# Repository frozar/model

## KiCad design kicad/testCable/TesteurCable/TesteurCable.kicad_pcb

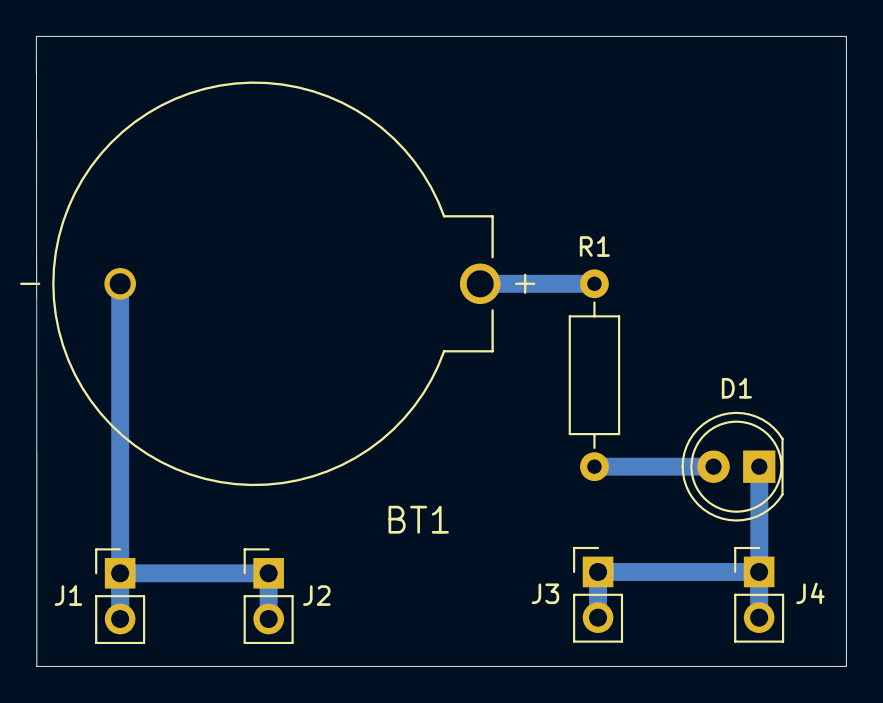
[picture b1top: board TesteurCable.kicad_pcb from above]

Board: 2 copper layers, 45.0 x 35.0 mm, 7 parts (0 on the bottom side), 4 nets.

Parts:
BT1: BS-7; BAT_BS-7
D1: LED_Verte; LED_D5.0mm
J1, J3: Conn_01x02_Male; PinHeader_1x02_P2.54mm_Vertical
J2, J4: Conn_01x02_Female; PinHeader_1x02_P2.54mm_Vertical
R1: 200; R_Axial_DIN0207_L6.3mm_D2.5mm_P10.16mm_Horizontal

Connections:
unnamed: BT1.+, R1.2
unnamed: BT1.-, J1.1, J1.2, J2.1, J2.2
unnamed: D1.1, J3.1, J3.2, J4.1, J4.2
unnamed: D1.2, R1.1

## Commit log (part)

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2018-02-24 Add source of c++, python and fortran
2018-03-15 [CPP] Const reference example in cpp
2018-03-15 [RUST] Rename directory
2018-03-16 [RUST] Add project variables.
2018-03-16 [RUST] Add data_types project.
2018-03-19 [RUST] Add ownership project.
2018-03-20 [RUST] Add enum_pattern project.
2018-03-21 [RUST] Add complexe sub-module project.
2018-03-21 [RUST] Example of a test in communicator project.
2018-03-22 [RUST] Add hash_map_example project.
2018-03-23 [RUST] Add recoverable_errors project.
2018-03-26 [RUST] Add project generics_motivation.
2018-03-27 [RUST] Fix the implementation of largest function thanks to trait bounds.
2018-03-28 [RUST] Add a projet about test writing.
2018-03-29 [RUST] WIP: Add project minigrep.
2018-03-31 [RUST] Implement case insensitive search. Use error channel to print error message.
2018-04-03 [RUST] Add project about closure.
2018-04-10 [RUST] Add projet minigrep which use closure and iterator.
2018-04-12 [RUST] Add project about cargo workspace
2018-04-16 [RUST] Add project about deref trait.
2018-04-16 [RUST] Add project about interior mutability pattern.
2018-04-17 [RUST] Add a project which show an example of memory leak in Rust.
2018-04-17 [RUST] Add project about mutex.
2018-04-19 [GIT] Add a .gitignore file
2018-04-19 [PYTHON] Add a tiny python example file.
2018-04-25 [PYTHRAN] Add example of numpy.dot
2018-07-09 [RUST] Add project about state pattern, the oriented-object way.
2018-07-10 [RUST] A way to finish the proposed exercices in ch17-03
2018-07-31 [PYTHON] Finalisation of the sierpinski animation.
2018-08-03 [PYTHON] WIP ast_dump.py program.
2018-08-06 [PYTHON] Functionnal AST dump program.
2018-10-08 Example of override.
2018-11-06 [CPP] Add an example of singleton without memory leak.
2018-11-06 [CPP] Add an example of singleton WIHTOUT memory leak using an abstract interface to hide implementation.
2019-01-30 [CPP] Add a trait example.
2019-02-11 [RUST] Add the directory the_book under rust section.
2019-02-16 [REACT] Add seasons example application.
2019-04-08 [CPP] Check if a unique_ptr is valid (contain something) or not.
2019-05-08 [ELM] Add an example of form (kind of).
2019-05-13 [ELM] Add example of randomness
2019-05-21 [ELM] Add the time example.
2019-05-31 [ELM] WIP application 8 queens problem.
2019-08-31 [CLJ] Challenge of the week: regular polygons.
2019-09-14 [CLJ] Challenge of the week: knights jam.
2019-09-25 [CLJS] tutorial-03
2019-09-27 [CLJS] tutorial-05
2019-10-19 [NODEJS] Add hello world.
2020-01-01 [CLOJURE] Add a basic example of ring application.
2020-01-18 [CLJ] Add the 'majuscule' and 'factoriel' examples.
2020-02-25 [CLJS] Simple move.
2020-03-26 [CLJ] Add example of clojure macro.
2020-04-17 Add a clojure example of permutation computation.
2020-08-30 WebGL2: Reorganise repository.
2020-08-30 WebGL: add example 2D matrix usage.
2020-09-02 WebGL: add example of camera manipulation.
2020-09-07 WebGL: add examples on gl.POINTS
2020-09-16 Firebase: add basic example to read/write to firestore database.
2020-09-17 Finish example clojurescript firestore.
2020-10-01 React: lifecycle methods example.
2020-10-05 React: hook usage example and handmade router.
2020-10-07 React: example of Redux application using get requests.
2020-10-10 React: finish the streaming application example.
2020-11-15 Codingame: challenge of the week
2020-12-17 Material-ui: finish section 3 of the course.
2020-12-23 ignore node_modules directories.
2020-12-26 Material-ui: finish section 8 of the course.
2020-12-29 Material-ui: finish section 11 of the course.
2020-12-31 Material-ui: finish section 14 of the course.
2021-01-06 Bump axios from 0.20.0 to 0.21.1 in /react/udemy/074-pics
    Bumps [axios](https://github.com/axios/axios) from 0.20.0 to 0.21.1.
    - [Release notes](https://github.com/axios/axios/releases)
    - [Changelog](https://github.com/axios/axios/blob/v0.21.1/CHANGELOG.md)
    - [Commits](https://github.com/axios/axios/compare/v0.20.0...v0.21.1)
2021-01-08 Material-ui: better handling of active index and navigation in general.
2021-01-31 HZV: Add almost everything from hzv directory: big saving of code.
2021-01-31 Add Elm ressources
2021-01-31 Webaudio: basic example.
2021-02-06 WIP: tree product, not correct results in alll case.
2021-02-13 Try some optimisation on the tree_produt problem.
2021-04-01 Bump y18n from 4.0.0 to 4.0.1 in /firebase/firestore/cljs/01-firestore
    Bumps [y18n](https://github.com/yargs/y18n) from 4.0.0 to 4.0.1.
    - [Release notes](https://github.com/yargs/y18n/releases)
    - [Changelog](https://github.com/yargs/y18n/blob/master/CHANGELOG.md)
    - [Commits](https://github.com/yargs/y18n/commits)
2021-04-17 Fonctional example of esp card send RFID uid via post request.
2021-04-29 Use the WifiManager library in the esp read RFID example.
2021-05-06 Add example of oled + arduino: koch snowflake.
2021-05-12 Bump @grpc/grpc-js in /firebase/firestore/cljs/01-firestore
    Bumps [@grpc/grpc-js](https://github.com/grpc/grpc-node) from 1.1.6 to 1.3.1.
    - [Release notes](https://github.com/grpc/grpc-node/releases)
    - [Commits](https://github.com/grpc/grpc-node/compare/@grpc/grpc-js@1.1.6...@grpc/grpc-js@1.3.1)
2021-06-07 Add example of Q-learning approach from hands on q learning with python.
2021-06-09 Follow example of KiCAD circuit from UIT Nantes.
2021-06-23 Add example KiCAD of testeurCable.
2021-06-23 Add example of Spring boot accessing data through JPA.
2021-06-23 Use spring boot to setup the GET route api/v1/person: allow to retrieve all people in DB.
2021-06-23 Try to add annotation to constraint Person instanciation.
2021-06-24 Rename directory 'youtube-demo' -> 'youtube-demo-2019'
2021-06-26 Add example 'amigoscode-demo-2021'
2021-08-29 Add a svelte demo application.
2021-08-30 Amigoscode project 2019, wip.
2021-09-09 Ignore gerber output directory.
2022-01-16 Add gulp tutorial example.
2022-01-16 Improve README
2022-01-24 Bump nanoid from 3.1.20 to 3.2.0 in /formik/formik-controls-demo
    Bumps [nanoid](https://github.com/ai/nanoid) from 3.1.20 to 3.2.0.
    - [Release notes](https://github.com/ai/nanoid/releases)
    - [Changelog](https://github.com/ai/nanoid/blob/main/CHANGELOG.md)
    - [Commits](https://github.com/ai/nanoid/compare/3.1.20...3.2.0)
    ---
    updated-dependencies:
2022-01-28 Remove the environment variable PARCEL_WORKER_BACKEND fix.
2022-01-28 Bump tmpl in /java/spring/amigoscode-test/src/frontend
    Bumps [tmpl](https://github.com/daaku/nodejs-tmpl) from 1.0.4 to 1.0.5.
    - [Release notes](https://github.com/daaku/nodejs-tmpl/releases)
    - [Commits](https://github.com/daaku/nodejs-tmpl/commits/v1.0.5)
    ---
    updated-dependencies:
    - dependency-name: tmpl
2022-02-06 Add codingame the_travelling_salesman_problem.rs
2022-02-07 [CG] rectangle_partition.rs
2022-02-27 Add simple example of c program.
2022-04-01 Bump minimist from 1.2.5 to 1.2.6 in /parcel
    Bumps [minimist](https://github.com/substack/minimist) from 1.2.5 to 1.2.6.
    - [Release notes](https://github.com/substack/minimist/releases)
    - [Commits](https://github.com/substack/minimist/compare/1.2.5...1.2.6)
    ---
    updated-dependencies:
    - dependency-name: minimist
2022-04-03 Bump minimist in /java/spring/amigoscode-test/src/frontend
    Bumps [minimist](https://github.com/substack/minimist) from 1.2.5 to 1.2.6.
    - [Release notes](https://github.com/substack/minimist/releases)
    - [Commits](https://github.com/substack/minimist/compare/1.2.5...1.2.6)
    ---
    updated-dependencies:
    - dependency-name: minimist
2022-06-06 Bump nalgebra from 0.17.0 to 0.27.1 in /rust/pythagorean_triples
    Bumps [nalgebra](https://github.com/dimforge/nalgebra) from 0.17.0 to 0.27.1.
    - [Release notes](https://github.com/dimforge/nalgebra/releases)
    - [Changelog](https://github.com/dimforge/nalgebra/blob/dev/CHANGELOG.md)
    - [Commits](https://github.com/dimforge/nalgebra/compare/v0.17...v0.27.1)
    ---
    updated-dependencies:
2022-06-20 WIP: codingame challenge.
2022-06-20 Bump async from 2.6.3 to 2.6.4 in /react/udemy/243-blog
    Bumps [async](https://github.com/caolan/async) from 2.6.3 to 2.6.4.
    - [Release notes](https://github.com/caolan/async/releases)
    - [Changelog](https://github.com/caolan/async/blob/v2.6.4/CHANGELOG.md)
    - [Commits](https://github.com/caolan/async/compare/v2.6.3...v2.6.4)
    ---
    updated-dependencies:
2022-06-20 Bump eventsource from 1.0.7 to 1.1.2 in /react/udemy/226-songs
    Bumps [eventsource](https://github.com/EventSource/eventsource) from 1.0.7 to 1.1.2.
    - [Release notes](https://github.com/EventSource/eventsource/releases)
    - [Changelog](https://github.com/EventSource/eventsource/blob/master/HISTORY.md)
    - [Commits](https://github.com/EventSource/eventsource/compare/v1.0.7...v1.1.2)
    ---
    updated-dependencies:
2022-06-20 Bump minimist from 1.2.5 to 1.2.6 in /react/udemy/243-blog
    Bumps [minimist](https://github.com/substack/minimist) from 1.2.5 to 1.2.6.
    - [Release notes](https://github.com/substack/minimist/releases)
    - [Commits](https://github.com/substack/minimist/compare/1.2.5...1.2.6)
    ---
    updated-dependencies:
    - dependency-name: minimist
2022-06-20 Codingame challenge ligue Bois 1.
2022-11-12 Bump minimatch and serve-handler in /parcel
    Bumps [minimatch](https://github.com/isaacs/minimatch) and [serve-handler](https://github.com/zeit/serve-handler). These dependencies needed to be updated together.
    Updates `minimatch` from 3.0.4 to 3.1.2
    - [Release notes](https://github.com/isaacs/minimatch/releases)
    - [Commits](https://github.com/isaacs/minimatch/compare/v3.0.4...v3.1.2)
    Updates `serve-handler` from 6.1.3 to 6.1.5
    - [Release notes](https://github.com/zeit/serve-handler/releases)
2022-12-23 Bump jsonwebtoken from 8.5.1 to 9.0.0 in /nodejs/jwt
    Bumps [jsonwebtoken](https://github.com/auth0/node-jsonwebtoken) from 8.5.1 to 9.0.0.
    - [Release notes](https://github.com/auth0/node-jsonwebtoken/releases)
    - [Changelog](https://github.com/auth0/node-jsonwebtoken/blob/master/CHANGELOG.md)
    - [Commits](https://github.com/auth0/node-jsonwebtoken/compare/v8.5.1...v9.0.0)
    ---
    updated-dependencies:
2023-01-26 Bump ua-parser-js in /clojurescript/hello-shadow-cljs
    Bumps [ua-parser-js](https://github.com/faisalman/ua-parser-js) from 0.7.21 to 0.7.33.
    - [Release notes](https://github.com/faisalman/ua-parser-js/releases)
    - [Changelog](https://github.com/faisalman/ua-parser-js/blob/master/changelog.md)
    - [Commits](https://github.com/faisalman/ua-parser-js/compare/0.7.21...0.7.33)
    ---
    updated-dependencies:
2023-03-03 Bump minimist and mkdirp in /clojurescript/hello-shadow-cljs
    Bumps [minimist](https://github.com/minimistjs/minimist) and [mkdirp](https://github.com/isaacs/node-mkdirp). These dependencies needed to be updated together.
    Updates `minimist` from 0.0.8 to 1.2.8
    - [Release notes](https://github.com/minimistjs/minimist/releases)
    - [Changelog](https://github.com/minimistjs/minimist/blob/main/CHANGELOG.md)
    - [Commits](https://github.com/minimistjs/minimist/compare/v0.0.8...v1.2.8)
    Updates `mkdirp` from 0.5.1 to 0.5.6
